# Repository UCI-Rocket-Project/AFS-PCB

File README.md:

# UCIRP Avionics Flight Sensor (AFS)
v1.1 "Rigel" (a star in Orion's constellation)

The board includes: 
- [Adafruit BMP388](https://www.amazon.com/Adafruit-BMP388-Precision-Barometric-Altimeter/dp/B07JXYK9ZB) Barometric and Pressure Sensor
- [Hitlego MPU-6050](https://www.amazon.com/HiLetgo-MPU-6050-Accelerometer-Gyroscope-Converter/dp/B01DK83ZYQ/ref=pd_ybh_a_1?_encoding=UTF8&refRID=VTDTAEY02AXR1SPZ293G&th=1) Accelerometer and Gyroscope
- [Adafruit Ultimate GPS](https://www.adafruit.com/product/746#description)
- [Digi XBee-PRO XSC S3B](https://www.mouser.com/ProductDetail/Gravitech/XBee-USB?qs=Vxac6xGyzPnMlpwH9hhfHQ%3D%3D) 
- [Sparkfun XBee Adapter](https://www.sparkfun.com/products/11373)
- Teensy 4.1
- [Linear Regulator (9V -> 5V)](https://www.digikey.com/en/products/detail/stmicroelectronics/L7805CV/585964)

Communication Protocols Used:
| Component  | Communication Protocol | 
| ------------- | ------------- |
| BMP388  | SPI  | 
| ECU 1.5 "Orion" | I2C (Wire) |
| GPS  | UART (Serial 2) |
| MPU-6050  | I2C (Wire 1)  |
| SD Module | SPI |
| XBEE  | UART (Serial 6) |

Pinouts:

BMP
- CS	 -> 10 CS
- SDI  -> 11 MOSI
- SDO  -> 12 MISO
- SCK  -> 13 SCK

ECU 1.5 "Orion"
- SDA2  -> 18 SDA
- SCL2  -> 19 SCL

GPS (Serial2 port in Teensy 4.1)
- TX	 -> 7 RX2
- RX	 -> 8 TX2

MPU (Wire1 port in Teensy 4.1)
- SDA  -> 17 SDA1
- SCL	 -> 16 SCL1

SD Module 
- MISO -> 39 MISO1
- MOSI -> 26 MOSI1
- SCK  -> 27 SCK1
- CS   -> 38 CS1

XBEE (Serial6 port in Teensy 4.1)
- DOUT -> 25  RX6
- DIN  -> 24 TX6

## Used Packages
- Teensy 4.1 [symbol](https://github.com/XenGi/teensy_library) and [footprint](https://github.com/XenGi/teensy.pretty). Related files and license is located under `/teensylib`.

## Notes
- The board requires an external 9V battery to power sensors and the Teensy. The onboard regulator will step down to 5V and provide stable 5V power.
- The GPS uses an optional "CR1220 coin cell to keep the RTC running and allow warm starts"
- The XBee module (not on AFS PCB) mounts on top of the XBee USB adapter. The USB adapter board has power and serial pass-through to the XBee module
- The board was renamed from "Avionics Test Payload (ATP)" to "Avionics Flight Sensor (AFS)"

### v1.1
- Changed [Adafruit XBee USB Adapter](https://www.adafruit.com/product/247?gclid=Cj0KCQiA1sucBhDgARIsAFoytUtwdYkYjMLGpFy2WvyzD8O8x4Ewsu3eSLwTMnisukgy84cH7zYznMQaAjZiEALw_wcB) to [Sparkfun XBee Adapter](https://www.sparkfun.com/products/11373)
- XBee receives 5V from regulator, instead of 3.3V from Teensy. During testing we found out that Teensy did not supply enough power for Xbee communication and after sending 1 or 2 packages of data, the Teensy would stop working.
- Regulator is flipped, so we can attach a heat sink

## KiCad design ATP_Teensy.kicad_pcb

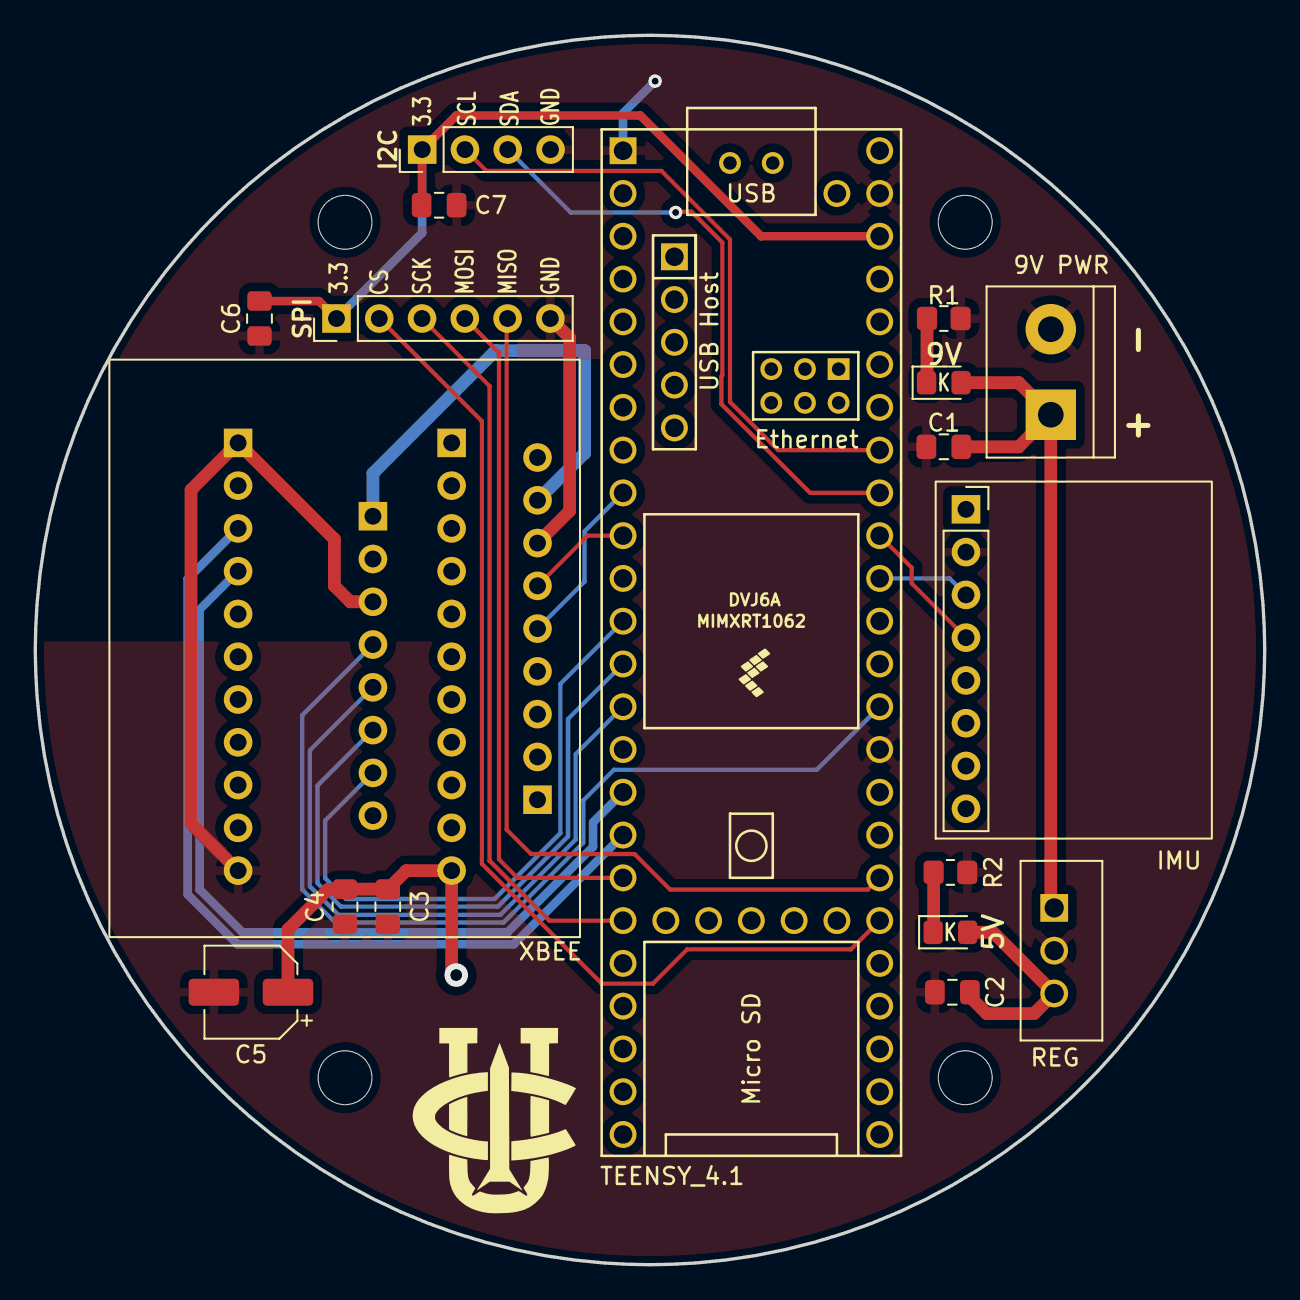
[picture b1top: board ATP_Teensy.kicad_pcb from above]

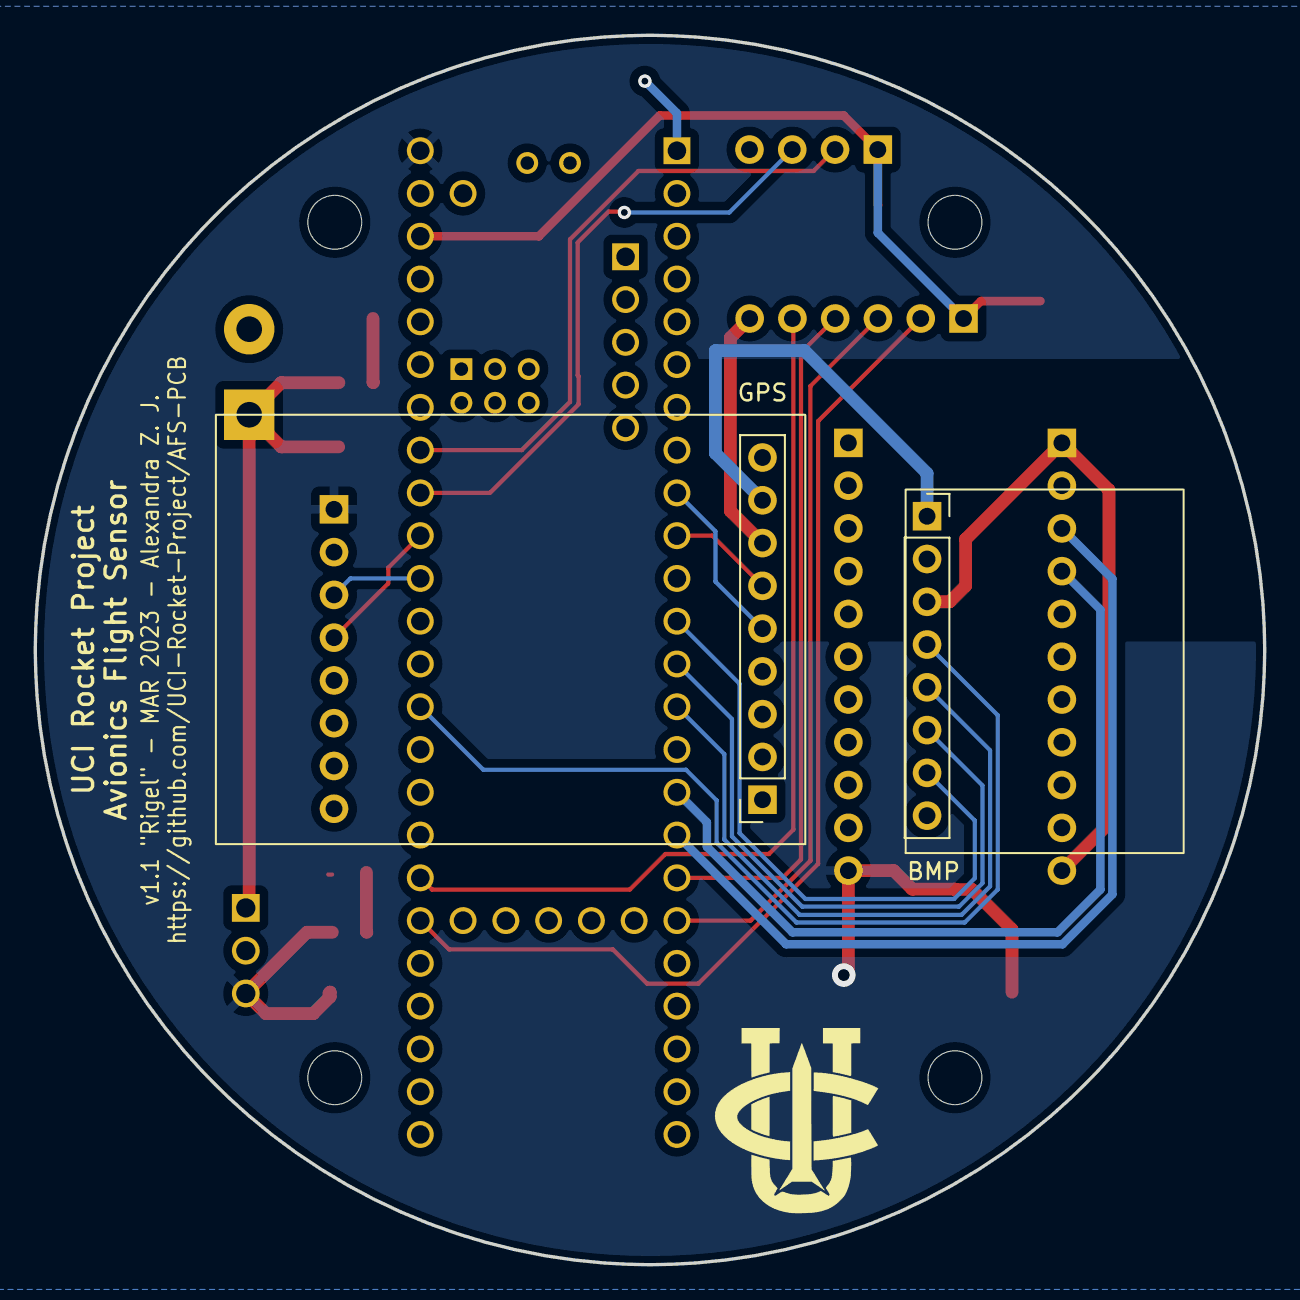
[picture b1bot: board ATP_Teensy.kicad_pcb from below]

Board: 2 copper layers, 73.0 x 73.0 mm, 26 parts (3 on the bottom side), 22 nets.

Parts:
5V, 9V: LED; LED_0805_2012Metric_Pad1.15x1.40mm_HandSolder
9V PWR: Screw_Terminal_01x02; TerminalBlock_bornier-2_P5.08mm
BMP: BMP388_3966; BMP_board
C1, C2: 10nF; C_0805_2012Metric_Pad1.18x1.45mm_HandSolder
C3: 47pF; C_0805_2012Metric_Pad1.18x1.45mm_HandSolder
C4, C6, C7: 1uF; C_0805_2012Metric_Pad1.18x1.45mm_HandSolder
C5: 10uF, 50V; CP_Elec_5x5.4
GPS: GPS; GPS_board
Ge: LOGO; UCIRP_logo
Ge#2: LOGO; UCIRP_logo
I2C: Conn_01x04_Male; PinHeader_1x04_P2.54mm_Vertical
IMU: MPU6050; IMU_board
J2, J3, J4, J5: Conn_01x01; MountingHole_3.2mm_M3
R1: 290R; R_0805_2012Metric_Pad1.20x1.40mm_HandSolder
R2: 90R; R_0805_2012Metric_Pad1.20x1.40mm_HandSolder
REG: L7805CV
SPI: Conn_01x06_Male; PinHeader_1x06_P2.54mm_Vertical
TEENSY_4.1: Teensy4.1; Teensy41
XBEE: XBee_SparkfunRegulatedAdapter; XBee_SparkfunAdapter

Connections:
+3.3V: C6.2, C7.2, I2C.1, SPI.1, TEENSY_4.1.46 (3V3)
+5V: 5V.2 (A), BMP.1 (VIN), C2.2, C3.2, C4.2, C5.1, GPS.8 (VIN), IMU.1 (VCC), REG.3 (OUT), TEENSY_4.1.48 (VIN), XBEE.22 (5V_IN)
+9V: 9V.2 (A), 9V PWR.1, C1.2, REG.1 (IN)
BMP_CS: BMP.7 (CS), TEENSY_4.1.12 (10_CS_MQSR)
BMP_SCK: BMP.4 (SCK), TEENSY_4.1.35 (13_SCK_LED)
BMP_SDI: BMP.6 (SDI), TEENSY_4.1.13 (11_MOSI_CTX1)
BMP_SDO: BMP.5 (SDO), TEENSY_4.1.14 (12_MISO_MQSL)
ECU_SCL: I2C.2, TEENSY_4.1.41 (19_A5_SCL)
ECU_SDA: I2C.3, TEENSY_4.1.40 (18_A4_SDA)
GND: 9V PWR.2, BMP.3 (GND), C1.1, C2.1, C3.1, C4.1, C5.2, C6.1, C7.1, GPS.7 (GND), I2C.4, IMU.2 (GND), R1.2, R2.2, REG.2 (GND), SPI.6, TEENSY_4.1.1 (GND), TEENSY_4.1.34 (GND), TEENSY_4.1.47 (GND), XBEE.1 (GND), XBEE.11 (GND)
GPS_RX: GPS.6 (RX), TEENSY_4.1.10 (8_TX2_IN1)
GPS_TX: GPS.5 (TX), TEENSY_4.1.9 (7_RX2_OUT1A)
MPU_SCL: IMU.3 (SCL), TEENSY_4.1.38 (16_A2_RX4_SCL1)
MPU_SDA: IMU.4 (SDA), TEENSY_4.1.39 (17_A3_TX4_SDA1)
unnamed: 9V.1 (K), R1.1
unnamed: 5V.1 (K), R2.1
SD_CS: SPI.2, TEENSY_4.1.30 (38_CS1_IN1)
SD_MISO: SPI.5, TEENSY_4.1.31 (39_MISO1_OUT1A)
SD_MOSI: SPI.4, TEENSY_4.1.18 (26_A12_MOSI1)
SD_SCK: SPI.3, TEENSY_4.1.19 (27_A13_SCK1)
XBEE_DIN: TEENSY_4.1.16 (24_A10_TX6_SCL2), XBEE.4 (DIN)
XBEE_DOUT: TEENSY_4.1.17 (25_A11_RX6_SDA2), XBEE.3 (DOUT)

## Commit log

2022-10-31 add footprints
2022-12-03 Add LED indicators
2022-12-03 Add mounting holes
2022-12-10 Change BMP connection from I2C to SPI
2022-12-18 Add filtering capacitors for XBee
2022-12-18 Add notes to XBee adapter
2022-12-18 Replace 10uF CER CAP with 10uF ELE CAP
2022-12-19 Update notes on schematic
2023-02-16 added teeny ports
2023-02-28 Generated 3d files of AFS
2023-02-28 added spi and i2c connections, actual mounting holes, change xbee power input in the schematic
2023-03-06 v1.1 Layout done, change direction of reg, added spi and i2c extensions
2023-03-07 Add labels for layout, DRC run, v1.1 Gerber files generated

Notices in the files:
parts and their libraries:
Copyright 2021 Accelerated Designs. All rights reserved.
